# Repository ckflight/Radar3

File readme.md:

# FMCW3 Hardware Design

Custom 6-layer FPGA-based FMCW radar platform designed in KiCad for high-speed radar acquisition, RF processing, and FPGA DSP applications.

The project integrates:

- RF transmitter and dual receiver chains
- ADL5802 mixer stage
- ADA4940 IF signal conditioning
- LTC2292 high-speed ADC
- Artix-7 FPGA processing
- FT2232H USB FIFO streaming
- Multi-rail low-noise power architecture

---

# Overview

FMCW3 is a custom 5.8 GHz FMCW radar hardware platform built around the Xilinx XC7A35T Artix-7 FPGA.

The board is designed for:

- FMCW radar experiments
- SAR imaging
- Doppler processing
- Phase analysis
- FPGA DSP development
- Radar algorithm research

---

# Main Features

## FPGA

- Xilinx XC7A35T-FTG256
- MicroBlaze soft-core support
- SPI Flash boot
- JTAG debugging
- SD card support
- Parallel ADC interface

## RF Front-End

- HMC431LP4 VCO
- Dual RX channels
- ADL5802 active mixer
- Differential IF architecture
- ADA4940 differential amplifiers

## ADC

- LTC2292 dual-channel ADC
- 12-bit parallel interface
- Differential analog inputs
- FPGA synchronous acquisition

## USB

- FT2232H
- FT245 synchronous FIFO mode
- USB Type-C
- High-speed radar data streaming

---

# 6-Layer PCB Design

The board is designed as a controlled impedance 6-layer RF PCB.

## RF Transmission Line Rules

### Single-Ended 50Ω

- JLCPCB:
  - 0.156 mm trace width
- CST Simulation:
  - 0.17 mm trace width

### Differential 50Ω

- 0.4 mm differential pair width/spacing

### USB Differential Pair

- Target impedance:
  - 90Ω differential
- 0.23 mm width
- 0.13 mm spacing

Results:
- ~100Ω on Oshpark
- ~85Ω on JLCPCB

Accepted as operational for USB HS routing.

---

# RF Layout Notes

- Ground pour kept at least:
  - 3× substrate height away from RF traces
- Via stitching placed:
  - ~1 mm beside RF traces
  - ~0.6 mm from trace edge
- LO path uses smooth bends for impedance continuity
- ADC and IF lengths matched for improved phase consistency
- RF clearances and differential routing optimized
- Differential RF routing corrected for proper 50Ω behavior

---

# KiCad Project Structure

```text
FMCW3/
├── fpga.kicad_sch
├── adc.kicad_sch
├── usb.kicad_sch
├── power.kicad_sch
├── mixer.kicad_sch
├── if.kicad_sch
├── tx.kicad_sch
├── rx.kicad_sch
├── fmcw3.kicad_sch
├── fmcw3.kicad_pcb
└── README.md
```

---

# Design Targets

| Parameter | Value |
|---|---|
| Radar Type | FMCW |
| Frequency | 5.8 GHz |
| FPGA | XC7A35T |
| ADC | LTC2292 |
| Mixer | ADL5802 |
| IF Amplifier | ADA4940 |
| USB Interface | FT2232H |
| PCB Stackup | 6 Layer |
| CAD Tool | KiCad 9 |

---

# Related Repositories

FPGA Firmware:
https://github.com/ckflight/FMCW3

Radar Software:
https://github.com/ckflight/FMCW_RADAR

https://github.com/ckflight/FMCW_RADAR_2v2

AI Radar Experiments:
https://github.com/ckflight/RADAR_24GHZ_NEURAL_NETWORK

---

# Author

Cenk KESKİN

---

# License

This project is licensed under the GNU General Public License v3.0 (GPLv3).

You are free to use, modify, and distribute this software under the terms of the GPLv3 license.

Any distributed modifications or derivative works must also be released under the same license and include source code.

For full license text:

https://www.gnu.org/licenses/gpl-3.0.html

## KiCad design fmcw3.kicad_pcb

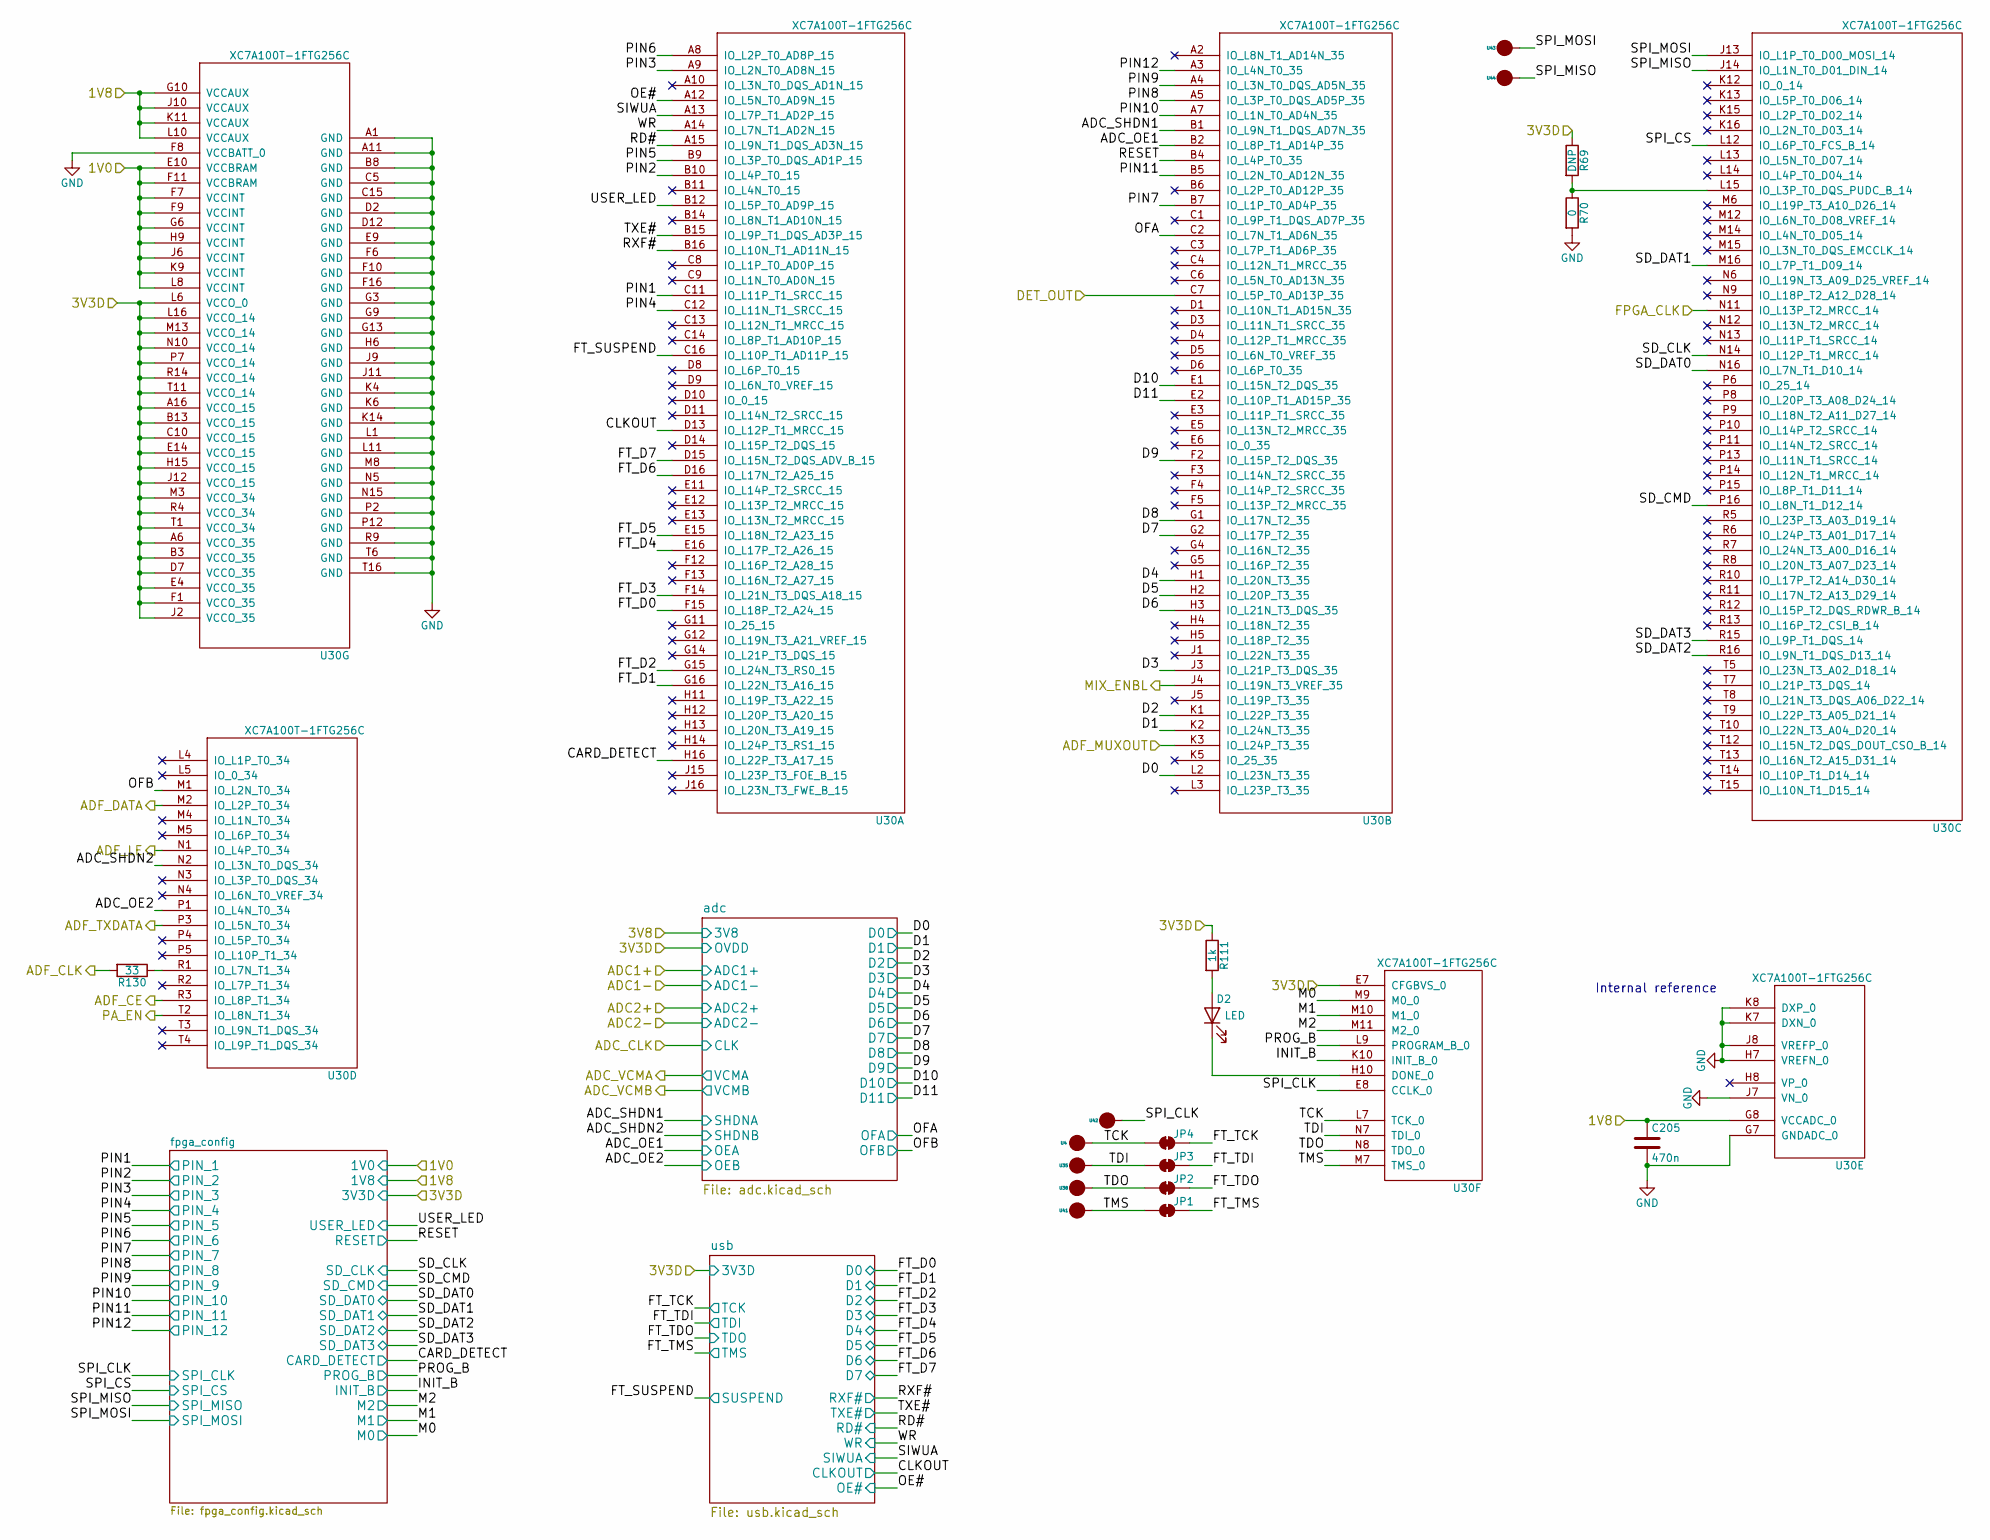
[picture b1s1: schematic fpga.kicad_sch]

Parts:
C205: 470n; SMD_0402
D2: LED; Diode_0603
JP1, JP2, JP3, JP4: SolderJumper_2_Bridged; SolderPad_2_Bridge
R69: DNP; SMD_0402
R70: 0; SMD_0402
R111: 1k; SMD_0402
R130: 33; SMD_0402
U4, U35, U38, U41, U42, U43, U44: SolderPad_1_Circle; SolderPad_1_1.0mm_SMD_Circle
U30: XC7A100T-1FTG256C; FTG256

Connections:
/1V0: U30.E10 (VCCBRAM), U30.F7 (VCCINT), U30.F9 (VCCINT), U30.F11 (VCCBRAM), U30.G6 (VCCINT), U30.H9 (VCCINT), U30.J6 (VCCINT), U30.K9 (VCCINT), U30.L8 (VCCINT); also elsewhere on the board
/1V8: C205.1, U30.G8 (VCCADC_0), U30.G10 (VCCAUX), U30.J10 (VCCAUX), U30.K11 (VCCAUX), U30.L10 (VCCAUX); also elsewhere on the board
/3V3D: R69.1, R111.1, U30.A6 (VCCO_35), U30.A16 (VCCO_15), U30.B3 (VCCO_35), U30.B13 (VCCO_15), U30.C10 (VCCO_15), U30.D7 (VCCO_35), U30.E4 (VCCO_35), U30.E7 (CFGBVS_0), U30.E14 (VCCO_15), U30.F1 (VCCO_35), U30.H15 (VCCO_15), U30.J2 (VCCO_35), U30.J12 (VCCO_15), U30.L6 (VCCO_0), U30.L16 (VCCO_14), U30.M3 (VCCO_34), U30.M13 (VCCO_14), U30.N10 (VCCO_14), U30.P7 (VCCO_14), U30.R4 (VCCO_34), U30.R14 (VCCO_14), U30.T1 (VCCO_34), U30.T11 (VCCO_14); also elsewhere on the board
/ADF_CE: U30.R3 (IO_L8P_T1_34); also elsewhere on the board
/ADF_CLK: R130.2; also elsewhere on the board
/ADF_DATA: U30.M2 (IO_L2P_T0_34); also elsewhere on the board
/ADF_LE: U30.N1 (IO_L4P_T0_34); also elsewhere on the board
/ADF_MUXOUT: U30.K3 (IO_L24P_T3_35); also elsewhere on the board
/ADF_TXDATA: U30.P3 (IO_L5N_T0_34); also elsewhere on the board
/DET_OUT: U30.C7 (IO_L5P_T0_AD13P_35); also elsewhere on the board
/FPGA_CLK: U30.N11 (IO_L13P_T2_MRCC_14); also elsewhere on the board
/MIX_ENBL: U30.J4 (IO_L19N_T3_VREF_35); also elsewhere on the board
/PA_EN: U30.T2 (IO_L8N_T1_34); also elsewhere on the board
/fpga/ADC_OE1: U30.B2 (IO_L8P_T1_AD14P_35); also elsewhere on the board
/fpga/ADC_OE2: U30.P1 (IO_L4N_T0_34); also elsewhere on the board
/fpga/ADC_SHDN1: U30.B1 (IO_L9N_T1_DQS_AD7N_35); also elsewhere on the board
/fpga/ADC_SHDN2: U30.N2 (IO_L3N_T0_DQS_34); also elsewhere on the board
/fpga/CARD_DETECT: U30.H16 (IO_L22P_T3_A17_15); also elsewhere on the board
/fpga/CLKOUT: U30.D13 (IO_L12P_T1_MRCC_15); also elsewhere on the board
/fpga/D0: U30.L2 (IO_L23N_T3_35); also elsewhere on the board
/fpga/D1: U30.K2 (IO_L24N_T3_35); also elsewhere on the board
/fpga/D2: U30.K1 (IO_L22P_T3_35); also elsewhere on the board
/fpga/D3: U30.J3 (IO_L21P_T3_DQS_35); also elsewhere on the board
/fpga/D4: U30.H1 (IO_L20N_T3_35); also elsewhere on the board
/fpga/D5: U30.H2 (IO_L20P_T3_35); also elsewhere on the board
/fpga/D6: U30.H3 (IO_L21N_T3_DQS_35); also elsewhere on the board
/fpga/D7: U30.G2 (IO_L17P_T2_35); also elsewhere on the board
/fpga/D8: U30.G1 (IO_L17N_T2_35); also elsewhere on the board
/fpga/D9: U30.F2 (IO_L15P_T2_DQS_35); also elsewhere on the board
/fpga/D10: U30.E1 (IO_L15N_T2_DQS_35); also elsewhere on the board
/fpga/D11: U30.E2 (IO_L10P_T1_AD15P_35); also elsewhere on the board
/fpga/FT_D0: U30.F15 (IO_L18P_T2_A24_15); also elsewhere on the board
/fpga/FT_D1: U30.G16 (IO_L22N_T3_A16_15); also elsewhere on the board
/fpga/FT_D2: U30.G15 (IO_L24N_T3_RS0_15); also elsewhere on the board
/fpga/FT_D3: U30.F14 (IO_L21N_T3_DQS_A18_15); also elsewhere on the board
/fpga/FT_D4: U30.E16 (IO_L17P_T2_A26_15); also elsewhere on the board
/fpga/FT_D5: U30.E15 (IO_L18N_T2_A23_15); also elsewhere on the board
/fpga/FT_D6: U30.D16 (IO_L17N_T2_A25_15); also elsewhere on the board
/fpga/FT_D7: U30.D15 (IO_L15N_T2_DQS_ADV_B_15); also elsewhere on the board
/fpga/FT_SUSPEND: U30.C16 (IO_L10P_T1_AD11P_15); also elsewhere on the board
/fpga/FT_TCK: JP4.2 (B); also elsewhere on the board
/fpga/FT_TDI: JP3.2 (B); also elsewhere on the board
/fpga/FT_TDO: JP2.2 (B); also elsewhere on the board
/fpga/FT_TMS: JP1.2 (B); also elsewhere on the board
/fpga/INIT_B: U30.K10 (INIT_B_0); also elsewhere on the board
/fpga/M0: U30.M9 (M0_0); also elsewhere on the board
/fpga/M1: U30.M10 (M1_0); also elsewhere on the board
/fpga/M2: U30.M11 (M2_0); also elsewhere on the board
/fpga/OE#: U30.A12 (IO_L5N_T0_AD9N_15); also elsewhere on the board
/fpga/OFA: U30.C2 (IO_L7N_T1_AD6N_35); also elsewhere on the board
/fpga/OFB: U30.M1 (IO_L2N_T0_34); also elsewhere on the board
/fpga/PIN1: U30.C11 (IO_L11P_T1_SRCC_15); also elsewhere on the board
/fpga/PIN2: U30.B10 (IO_L4P_T0_15); also elsewhere on the board
/fpga/PIN3: U30.A9 (IO_L2N_T0_AD8N_15); also elsewhere on the board
/fpga/PIN4: U30.C12 (IO_L11N_T1_SRCC_15); also elsewhere on the board
/fpga/PIN5: U30.B9 (IO_L3P_T0_DQS_AD1P_15); also elsewhere on the board
/fpga/PIN6: U30.A8 (IO_L2P_T0_AD8P_15); also elsewhere on the board
/fpga/PIN7: U30.B7 (IO_L1P_T0_AD4P_35); also elsewhere on the board
/fpga/PIN8: U30.A5 (IO_L3P_T0_DQS_AD5P_35); also elsewhere on the board
/fpga/PIN9: U30.A4 (IO_L3N_T0_DQS_AD5N_35); also elsewhere on the board
/fpga/PIN10: U30.A7 (IO_L1N_T0_AD4N_35); also elsewhere on the board
/fpga/PIN11: U30.B5 (IO_L2N_T0_AD12N_35); also elsewhere on the board
/fpga/PIN12: U30.A3 (IO_L4N_T0_35); also elsewhere on the board
/fpga/PROG_B: U30.L9 (PROGRAM_B_0); also elsewhere on the board
/fpga/RD#: U30.A15 (IO_L9N_T1_DQS_AD3N_15); also elsewhere on the board
/fpga/RESET: U30.B4 (IO_L4P_T0_35); also elsewhere on the board
/fpga/RXF#: U30.B16 (IO_L10N_T1_AD11N_15); also elsewhere on the board
/fpga/SD_CLK: U30.N14 (IO_L12P_T1_MRCC_14); also elsewhere on the board
/fpga/SD_CMD: U30.P16 (IO_L8N_T1_D12_14); also elsewhere on the board
/fpga/SD_DAT0: U30.N16 (IO_L7N_T1_D10_14); also elsewhere on the board
/fpga/SD_DAT1: U30.M16 (IO_L7P_T1_D09_14); also elsewhere on the board
/fpga/SD_DAT2: U30.R16 (IO_L9N_T1_DQS_D13_14); also elsewhere on the board
/fpga/SD_DAT3: U30.R15 (IO_L9P_T1_DQS_14); also elsewhere on the board
/fpga/SIWUA: U30.A13 (IO_L7P_T1_AD2P_15); also elsewhere on the board
/fpga/SPI_CLK: U30.E8 (CCLK_0), U42.1; also elsewhere on the board
/fpga/SPI_CS: U30.L12 (IO_L6P_T0_FCS_B_14); also elsewhere on the board
/fpga/SPI_MISO: U30.J14 (IO_L1N_T0_D01_DIN_14), U44.1; also elsewhere on the board
/fpga/SPI_MOSI: U30.J13 (IO_L1P_T0_D00_MOSI_14), U43.1; also elsewhere on the board
/fpga/TCK: JP4.1 (A), U4.1, U30.L7 (TCK_0)
/fpga/TDI: JP3.1 (A), U30.N7 (TDI_0), U35.1
/fpga/TDO: JP2.1 (A), U30.N8 (TDO_0), U38.1
/fpga/TMS: JP1.1 (A), U30.M7 (TMS_0), U41.1
/fpga/TXE#: U30.B15 (IO_L9P_T1_DQS_AD3P_15); also elsewhere on the board
/fpga/USER_LED: U30.B12 (IO_L5P_T0_AD9P_15); also elsewhere on the board
/fpga/WR: U30.A14 (IO_L7N_T1_AD2N_15); also elsewhere on the board
GND: C205.2, R70.2, U30.A1 (GND), U30.A11 (GND), U30.B8 (GND), U30.C5 (GND), U30.C15 (GND), U30.D2 (GND), U30.D12 (GND), U30.E9 (GND), U30.F6 (GND), U30.F8 (VCCBATT_0), U30.F10 (GND), U30.F16 (GND), U30.G3 (GND), U30.G7 (GNDADC_0), U30.G9 (GND), U30.G13 (GND), U30.H6 (GND), U30.H7 (VREFN_0), U30.J7 (VN_0), U30.J8 (VREFP_0), U30.J9 (GND), U30.J11 (GND), U30.K4 (GND), U30.K6 (GND), U30.K7 (DXN_0), U30.K8 (DXP_0), U30.K14 (GND), U30.L1 (GND), U30.L11 (GND), U30.M8 (GND), U30.N5 (GND), U30.N15 (GND), U30.P2 (GND), U30.P12 (GND), U30.R9 (GND), U30.T6 (GND), U30.T16 (GND); also elsewhere on the board
unnamed: D2.2 (A), R111.2
unnamed: D2.1 (K), U30.H10 (DONE_0)
unnamed: R69.2, R70.1, U30.L15 (IO_L3P_T0_DQS_PUDC_B_14)
unnamed: R130.1, U30.R1 (IO_L7N_T1_34)

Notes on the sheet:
Internal reference

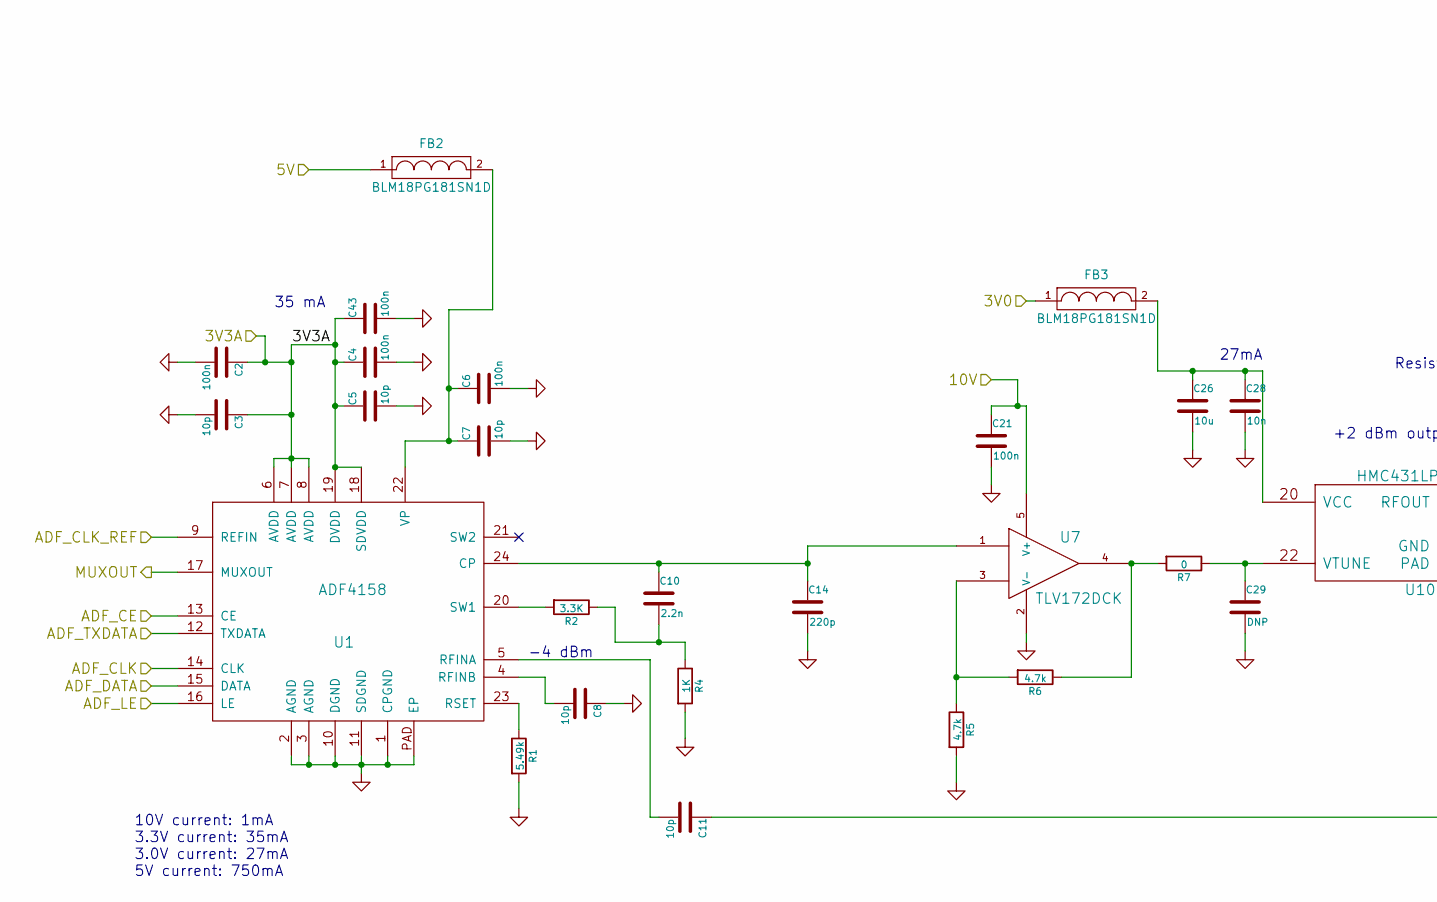
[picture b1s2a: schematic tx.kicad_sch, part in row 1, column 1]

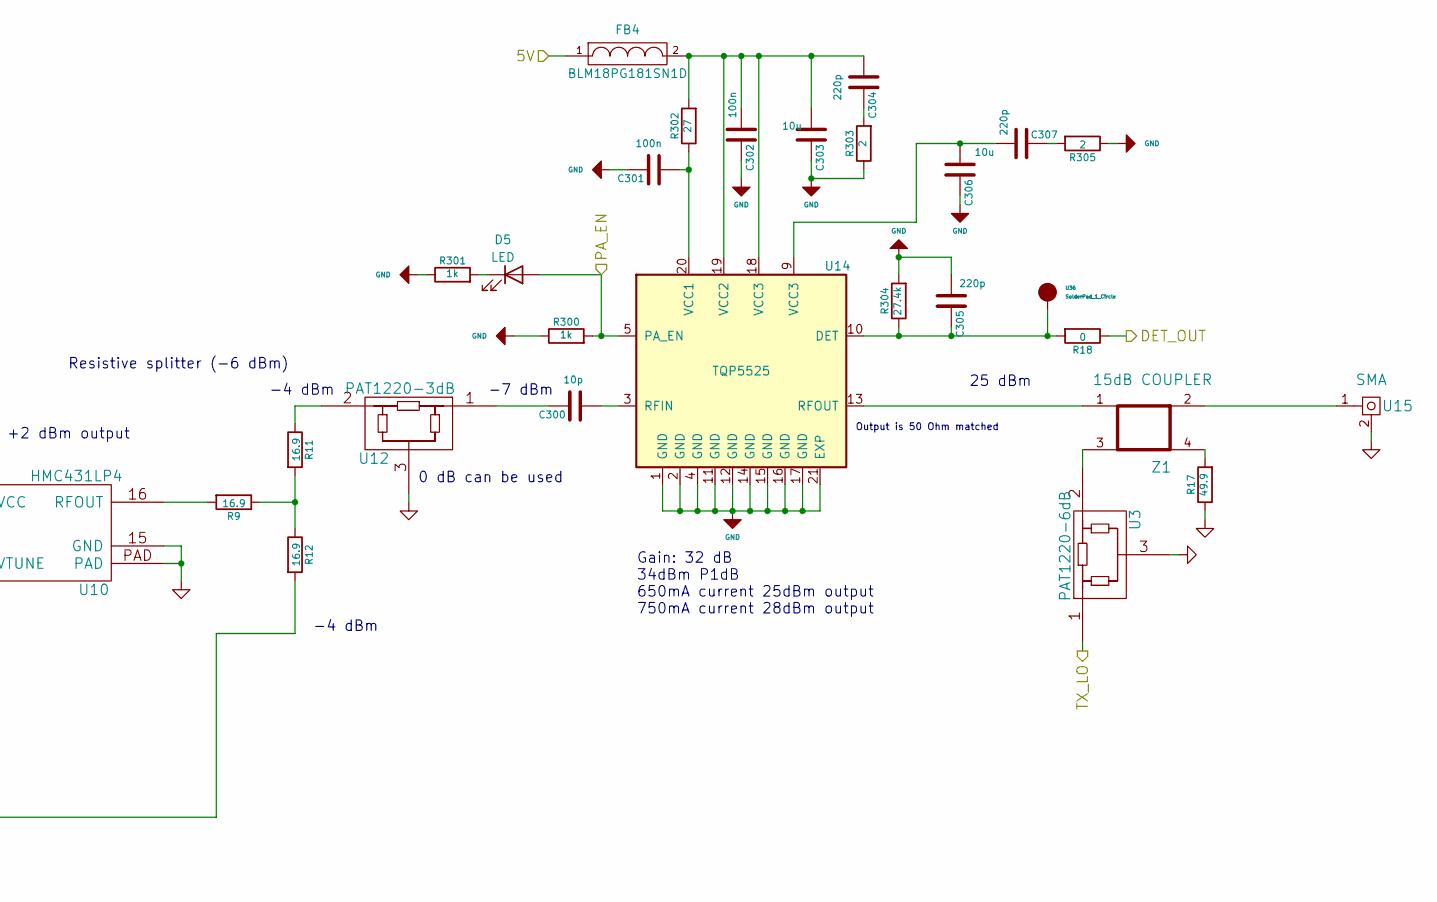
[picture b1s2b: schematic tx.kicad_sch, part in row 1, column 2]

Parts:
C2, C4, C6, C21, C43, C301, C302: 100n; SMD_0402
C3, C5, C7, C8, C11, C300: 10p; SMD_0402
C10: 2.2n; SMD_0402
C14, C304, C305, C307: 220p; SMD_0402
C26, C303, C306: 10u; SMD_0805
C28: 10n; SMD_0402
C29: DNP; SMD_0402
D5: LED; Diode_0603
FB2, FB3, FB4: BLM18PG181SN1D; SMD_0603
R1: 5.49k; SMD_0402
R2: 3.3K; SMD_0402
R4: 1K; SMD_0402
R5, R6: 4.7k; SMD_0402
R7, R18: 0; SMD_0402
R9, R11, R12: 16.9; SMD_0402
R17: 49.9; SMD_0402
R300, R301: 1k; SMD_0402
R302: 27; SMD_0402
R303, R305: 2; SMD_0603
R304: 27.4k; SMD_0402
U1: ADF4158; VFQFN-24
U3: PAT1220-6dB; PAT1220
U7: TLV172DCK; SOT-353_SC-70-5
U10: HMC431LP4; VQFN-24
U12: PAT1220-3dB; PAT1220
U14: TQP5525; QFN-20-1EP_4x4mm_P0.5mm_EP2.5x2.5mm_ThermalVias
U15: SMA; CONSMA003.062
U36: SolderPad_1_Circle; SolderPad_1_1.5mm_SMD_Circle
Z1: 15dB COUPLER; Directional_Coupler_15dB_0.169mm_v2

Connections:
/3V0: FB3.1; also elsewhere on the board
/3V3A: C2.1, C3.1, C4.1, C5.1, C43.1, U1.6 (AVDD), U1.7 (AVDD), U1.8 (AVDD), U1.18 (SDVDD), U1.19 (DVDD); also elsewhere on the board
/5V: FB2.1, FB4.1; also elsewhere on the board
/10V: C21.1, U7.5 (V+); also elsewhere on the board
/ADF_CE: U1.13 (CE); also elsewhere on the board
/ADF_CLK: U1.14 (CLK); also elsewhere on the board
/ADF_CLK_REF: U1.9 (REFIN); also elsewhere on the board
/ADF_DATA: U1.15 (DATA); also elsewhere on the board
/ADF_LE: U1.16 (LE); also elsewhere on the board
/ADF_MUXOUT: U1.17 (MUXOUT); also elsewhere on the board
/ADF_TXDATA: U1.12 (TXDATA); also elsewhere on the board
/DET_OUT: R18.1; also elsewhere on the board
/LO: U3.1; also elsewhere on the board
/PA_EN: D5.2 (A), R300.2, U14.5 (PA_EN); also elsewhere on the board
GND: C2.2, C3.2, C4.2, C5.2, C6.2, C7.2, C8.1, C14.2, C21.2, C26.2, C28.2, C29.2, C43.2, C301.1, C302.1, C303.1, C305.2, C306.1, R1.2, R4.2, R5.2, R17.1, R300.1, R301.1, R303.1, R304.2, R305.1, U1.1 (CPGND), U1.2 (AGND), U1.3 (AGND), U1.10 (DGND), U1.11 (SDGND), U1.PAD (EP), U3.3, U7.2 (V-), U10.15 (GND), U10.PAD, U12.3, U14.1 (GND), U14.2 (GND), U14.4 (GND), U14.11 (GND), U14.12 (GND), U14.14 (GND), U14.15 (GND), U14.16 (GND), U14.17 (GND), U14.21 (EXP), U15.2; also elsewhere on the board
unnamed: C10.2, R2.1, R4.1
unnamed: C11.1, R12.2
unnamed: C300.1, U12.1
unnamed: C304.1, R303.2
unnamed: C306.2, C307.2, U14.9 (VCC3)
unnamed: C307.1, R305.2
unnamed: D5.1 (K), R301.2
unnamed: R5.1, R6.2, U7.3
unnamed: R6.1, R7.2, U7.4
unnamed: R11.1, U12.2
unnamed: R9.1, R11.2, R12.1
unnamed: R17.2, Z1.4
unnamed: C10.1, C14.1, U1.24 (CP), U7.1
unnamed: C11.2, U1.5 (RFINA)
unnamed: C8.2, U1.4 (RFINB)
unnamed: R1.1, U1.23 (RSET)
unnamed: R2.2, U1.20 (SW1)
unnamed: C6.1, C7.1, FB2.2, U1.22 (VP)
unnamed: U3.2, Z1.3
unnamed: R9.2, U10.16 (RFOUT)
unnamed: C26.1, C28.1, FB3.2, U10.20 (VCC)
unnamed: C29.1, R7.1, U10.22 (VTUNE)
unnamed: C305.1, R18.2, R304.1, U14.10 (DET), U36.1
unnamed: C300.2, U14.3 (RFIN)
unnamed: U14.13 (RFOUT), Z1.1
unnamed: C301.2, R302.1, U14.20 (VCC1)
unnamed: C302.2, C303.2, C304.2, FB4.2, R302.2, U14.18 (VCC3), U14.19 (VCC2)
unnamed: U15.1, Z1.2

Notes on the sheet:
Resistive splitter (-6 dBm)
-4 dBm
10V current: 1mA 3.3V current: 35mA 3.0V current: 27mA 5V current: 750mA
+2 dBm output
35 mA
-7 dBm
27mA
Output is 50 Ohm matched
Gain: 32 dB 34dBm P1dB 650mA current 25dBm output 750mA current 28dBm output
0 dB can be used
25 dBm

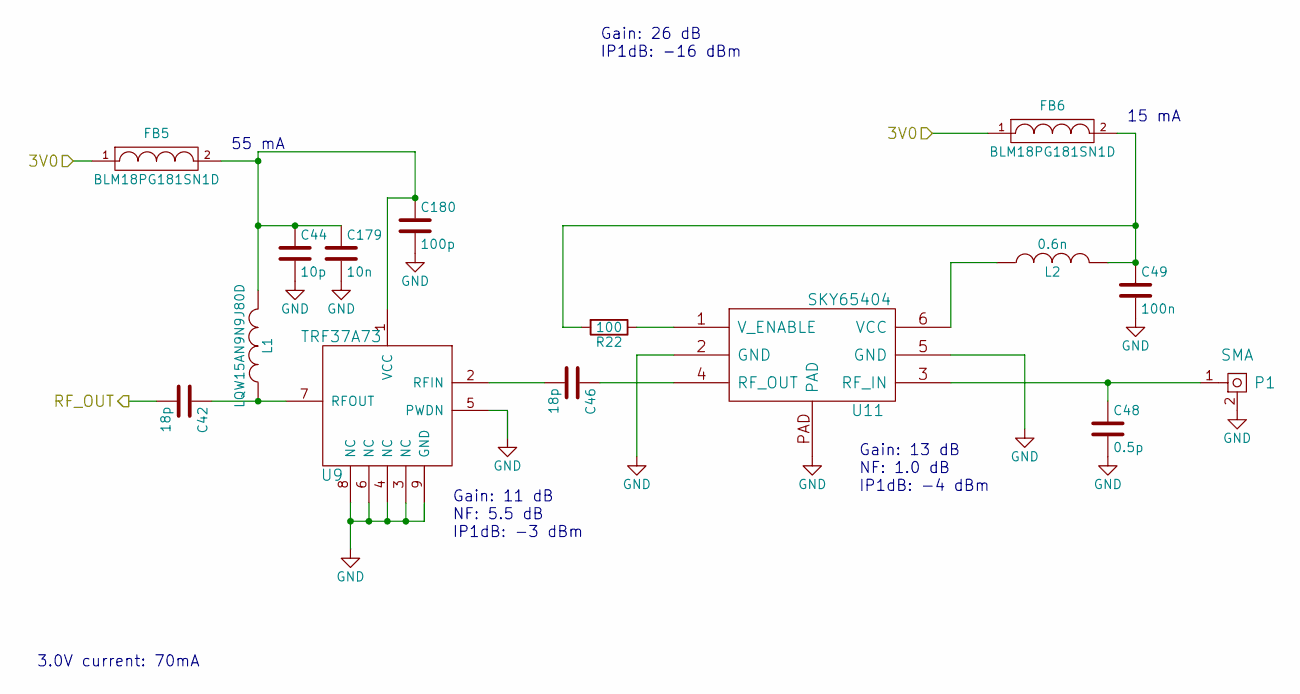
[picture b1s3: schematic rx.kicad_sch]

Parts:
C42, C46: 18p; SMD_0402
C44: 10p; SMD_0402
C48: 0.5p; SMD_0402
C49: 100n; SMD_0402
C179: 10n; SMD_0402
C180: 100p; SMD_0402
FB5, FB6: BLM18PG181SN1D; SMD_0603
L1: LQW15AN9N9J80D; SMD_0402
L2: 0.6n; SMD_0402
P1: SMA; CONSMA003.062
R22: 100; SMD_0402
U9: TRF37A73; DFN-8-1EP_2x2mm_Pitch0.5mm
U11: SKY65404; XFDFN-6

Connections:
/3V0: FB5.1, FB6.1; also elsewhere on the board
/RF1: C42.2; also elsewhere on the board
GND: C44.2, C48.2, C49.2, C179.2, C180.2, P1.2, U9.3 (NC), U9.4 (NC), U9.5 (PWDN), U9.6 (NC), U9.8 (NC), U9.9 (GND), U11.2 (GND), U11.5 (GND), U11.PAD; also elsewhere on the board
unnamed: C49.1, FB6.2, L2.2, R22.2
unnamed: C46.2, U9.2 (RFIN)
unnamed: C42.1, L1.1, U9.7 (RFOUT)
unnamed: C44.1, C179.1, C180.1, FB5.2, L1.2, U9.1 (VCC)
unnamed: C48.1, P1.1, U11.3 (RF_IN)
unnamed: C46.1, U11.4 (RF_OUT)
unnamed: L2.1, U11.6 (VCC)
unnamed: R22.1, U11.1 (V_ENABLE)

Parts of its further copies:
C52, C55: 18p; SMD_0402
C53: 10p; SMD_0402
C57: 0.5p; SMD_0402
C58: 100n; SMD_0402
C206: 10n; SMD_0402
C213: 100p; SMD_0402
FB7, FB8: BLM18PG181SN1D; SMD_0603
L3: LQW15AN9N9J80D; SMD_0402
L4: 0.6n; SMD_0402
P2: SMA; CONSMA003.062
R23: 100; SMD_0402
U13: TRF37A73; DFN-8-1EP_2x2mm_Pitch0.5mm
U16: SKY65404; XFDFN-6

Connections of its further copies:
/3V0: FB7.1, FB8.1; also elsewhere on the board
/RF2: C52.2; also elsewhere on the board
GND: C53.2, C57.2, C58.2, C206.2, C213.2, P2.2, U13.3 (NC), U13.4 (NC), U13.5 (PWDN), U13.6 (NC), U13.8 (NC), U13.9 (GND), U16.2 (GND), U16.5 (GND), U16.PAD; also elsewhere on the board
unnamed: C58.1, FB8.2, L4.2, R23.2
unnamed: C55.2, U13.2 (RFIN)
unnamed: C52.1, L3.1, U13.7 (RFOUT)
unnamed: C53.1, C206.1, C213.1, FB7.2, L3.2, U13.1 (VCC)
unnamed: C57.1, P2.1, U16.3 (RF_IN)
unnamed: C55.1, U16.4 (RF_OUT)
unnamed: L4.1, U16.6 (VCC)
unnamed: R23.1, U16.1 (V_ENABLE)

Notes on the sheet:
Gain: 11 dB NF: 5.5 dB IP1dB: -3 dBm
15 mA
Gain: 13 dB NF: 1.0 dB IP1dB: -4 dBm
3.0V current: 70mA
55 mA
Gain: 26 dB IP1dB: -16 dBm

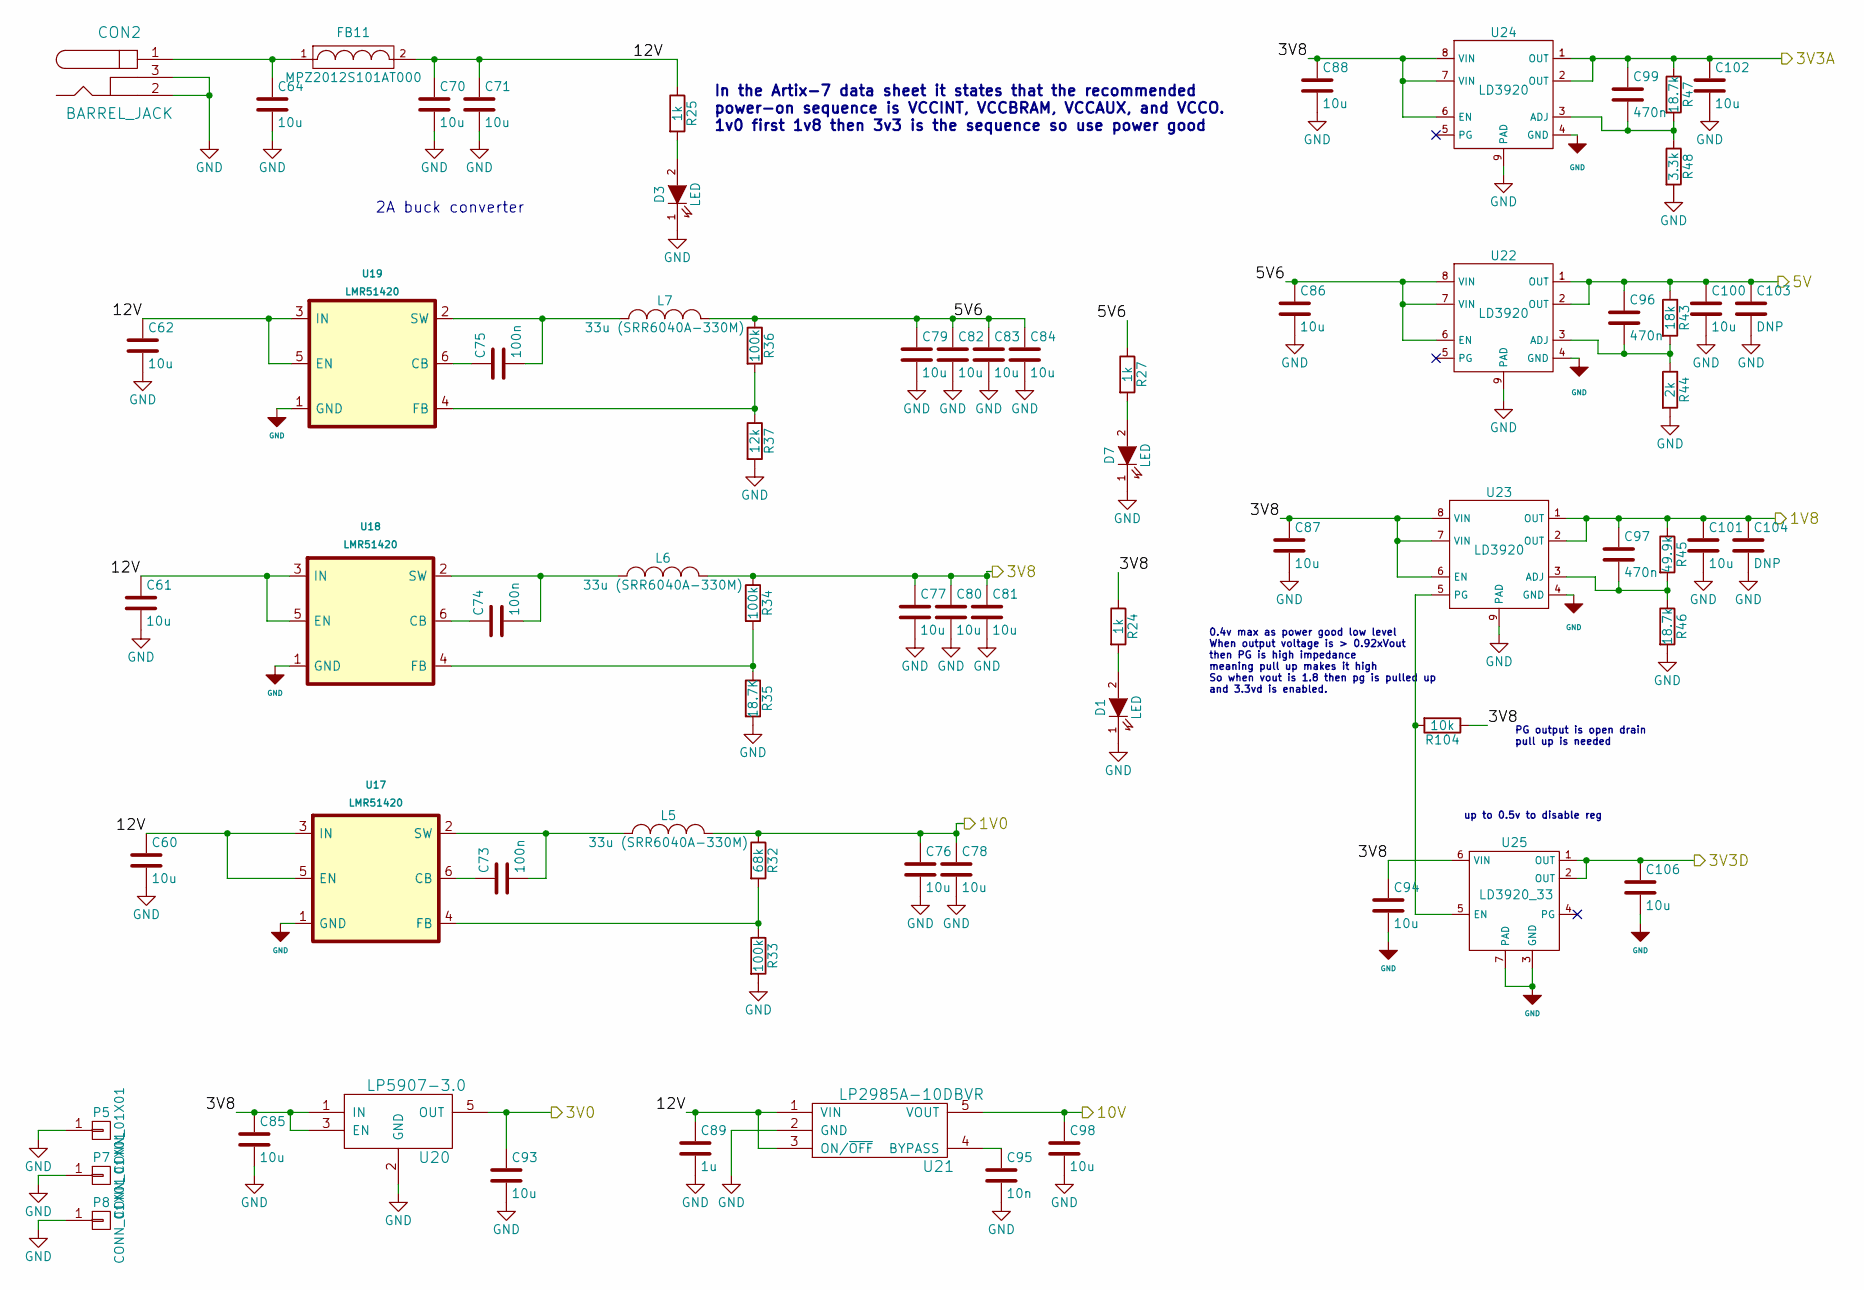
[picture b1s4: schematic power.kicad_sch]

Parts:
C60, C61, C62, C64, C70, C71, C76, C77, C78, C79, C80, C81, C82, C83, C84, C85, C86, C87, C88, C93, C94, C98, C100, C101, C102, C106: 10u; SMD_0805
C73, C74, C75: 100n; SMD_0402
C89: 1u; SMD_0603
C95: 10n; SMD_0402
C96, C97, C99: 470n; SMD_0402
C103, C104: DNP; SMD_0805
CON2: BARREL_JACK; BarrelJack
D1, D3, D7: LED; Diode_0603
FB11: MPZ2012S101AT000; SMD_0805
L5, L6, L7: 33u (SRR6040A-330M); SRR6040A
P5, P7, P8: CONN_01X01; MountingHole_3.2mm_M3_Pad_Via_mod
R24, R25, R27: 1k; SMD_0402
R32: 68k; SMD_0402
R33, R34, R36: 100k; SMD_0402
R35: 18.7K; SMD_0402
R37: 12k; SMD_0402
R43: 18k; SMD_0402
R44: 2k; SMD_0402
R45: 49.9k; SMD_0402
R46, R47: 18.7k; SMD_0402
R48: 3.3k; SMD_0402
R104: 10k; SMD_0402
U17, U18, U19: LMR51420; SOT23_6
U20: LP5907-3.0; SOT-23-5
U21: LP2985A-10DBVR; SOT-23-5
U22, U23, U24: LD3920; DFN-8-1EP_4x4mm_P0.8mm_EP2.3x3.24mm
U25: LD3920_33; DFN-6-1EP_3x3mm_P0.95mm_EP1.7x2.6mm

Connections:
/1V0: C76.1, C78.1, L5.2, R32.1; also elsewhere on the board
/1V8: C97.1, C101.1, C104.1, R45.1, U23.1 (OUT), U23.2 (OUT); also elsewhere on the board
/3V0: C93.1, U20.5 (OUT); also elsewhere on the board
/3V3A: C99.1, C102.1, R47.1, U24.1 (OUT), U24.2 (OUT); also elsewhere on the board
/3V3D: C106.1, U25.1 (OUT), U25.2 (OUT); also elsewhere on the board
/3V8: C77.1, C80.1, C81.1, C85.1, C87.1, C88.1, C94.1, L6.2, R24.1, R34.1, R104.1, U20.1 (IN), U20.3 (EN), U23.6 (EN), U23.7 (VIN), U23.8 (VIN), U24.6 (EN), U24.7 (VIN), U24.8 (VIN), U25.6 (VIN); also elsewhere on the board
/5V: C96.1, C100.1, C103.1, R43.1, U22.1 (OUT), U22.2 (OUT); also elsewhere on the board
/10V: C98.1, U21.5 (VOUT); also elsewhere on the board
/power/5V6: C79.1, C82.1, C83.1, C84.1, C86.1, L7.2, R27.1, R36.1, U22.6 (EN), U22.7 (VIN), U22.8 (VIN)
/power/12V: C60.1, C61.1, C62.1, C70.1, C71.1, C89.1, FB11.2, R25.1, U17.3 (IN), U17.5 (EN), U18.3 (IN), U18.5 (EN), U19.3 (IN), U19.5 (EN), U21.1 (VIN), U21.3 (ON/~OFF)
GND: C60.2, C61.2, C62.2, C64.2, C70.2, C71.2, C76.2, C77.2, C78.2, C79.2, C80.2, C81.2, C82.2, C83.2, C84.2, C85.2, C86.2, C87.2, C88.2, C89.2, C93.2, C94.2, C95.2, C98.2, C100.2, C101.2, C102.2, C103.2, C104.2, C106.2, CON2.2, CON2.3, D1.1 (K), D3.1 (K), D7.1 (K), P5.1, P7.1, P8.1, R33.2, R35.2, R37.2, R44.2, R46.2, R48.2, U17.1 (GND), U18.1 (GND), U19.1 (GND), U20.2 (GND), U21.2 (GND), U22.4 (GND), U22.9 (PAD), U23.4 (GND), U23.9 (PAD), U24.4 (GND), U24.9 (PAD), U25.3 (GND), U25.7 (PAD); also elsewhere on the board
unnamed: C64.1, CON2.1, FB11.1
unnamed: D1.2 (A), R24.2
unnamed: D3.2 (A), R25.2
unnamed: D7.2 (A), R27.2
unnamed: C73.1, U17.6 (CB)
unnamed: R32.2, R33.1, U17.4 (FB)
unnamed: C73.2, L5.1, U17.2 (SW)
unnamed: C74.1, U18.6 (CB)
unnamed: R34.2, R35.1, U18.4 (FB)
unnamed: C74.2, L6.1, U18.2 (SW)
unnamed: C75.1, U19.6 (CB)
unnamed: R36.2, R37.1, U19.4 (FB)
unnamed: C75.2, L7.1, U19.2 (SW)
unnamed: C95.1, U21.4 (BYPASS)
unnamed: C96.2, R43.2, R44.1, U22.3 (ADJ)
unnamed: C97.2, R45.2, R46.1, U23.3 (ADJ)
unnamed: R104.2, U23.5 (PG), U25.5 (EN)
unnamed: C99.2, R47.2, R48.1, U24.3 (ADJ)

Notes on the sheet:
up to 0.5v to disable reg
0.4v max as power good low level When output voltage is > 0.92xVout then PG is high impedance meaning pull up makes it high So when vout is 1.8 then pg is pulled up and 3.3vd is enabled.
PG output is open drain pull up is needed
In the Artix-7 data sheet it states that the recommended power-on sequence is VCCINT, VCCBRAM, VCCAUX, and VCCO. 1v0 first 1v8 then 3v3 is the sequence so use power good
2A buck converter

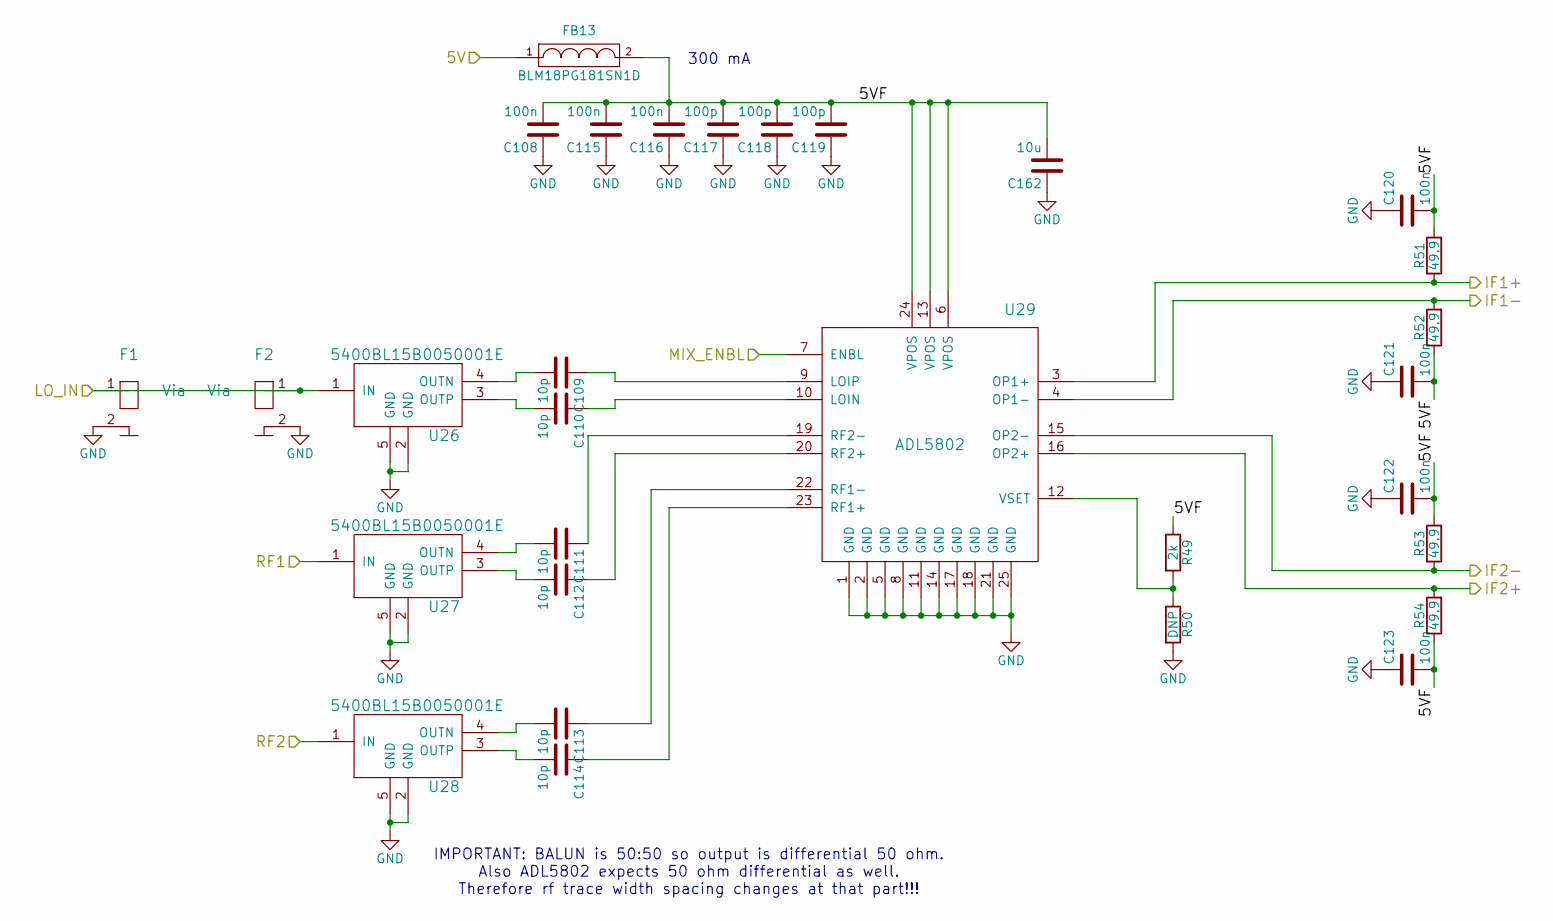
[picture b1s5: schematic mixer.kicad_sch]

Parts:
C108, C115, C116, C120, C121, C122, C123: 100n; SMD_0402
C109, C110, C111, C112, C113, C114: 10p; SMD_0402
C117, C118, C119: 100p; SMD_0402
C162: 10u; SMD_0805
F1, F2: Via; RF_via
FB13: BLM18PG181SN1D; SMD_0603
R49: 2k; SMD_0402
R50: DNP; SMD_0402
R51, R52, R53, R54: 49.9; SMD_0402
U26, U27, U28: 5400BL15B0050001E; 5400BL15B050E
U29: ADL5802; QFN-24-1EP_4x4mm_Pitch0.5mm

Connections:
/5V: FB13.1; also elsewhere on the board
/LO: F1.1, F2.1, U26.1 (IN); also elsewhere on the board
/MIX_ENBL: U29.7 (ENBL); also elsewhere on the board
/RF1: U27.1 (IN); also elsewhere on the board
/RF2: U28.1 (IN); also elsewhere on the board
/mixer/5VF: C108.2, C115.2, C116.2, C117.2, C118.2, C119.2, C120.2, C121.2, C122.2, C123.2, C162.2, FB13.2, R49.1, R51.2, R52.1, R53.2, R54.1, U29.6 (VPOS), U29.13 (VPOS), U29.24 (VPOS)
/mixer/IF1+: R51.1, U29.3 (OP1+); also elsewhere on the board
/mixer/IF1-: R52.2, U29.4 (OP1-); also elsewhere on the board
/mixer/IF2+: R54.2, U29.16 (OP2+); also elsewhere on the board
/mixer/IF2-: R53.1, U29.15 (OP2-); also elsewhere on the board
GND: C108.1, C115.1, C116.1, C117.1, C118.1, C119.1, C120.1, C121.1, C122.1, C123.1, C162.1, F1.2, F2.2, R50.2, U26.2 (GND), U26.5 (GND), U27.2 (GND), U27.5 (GND), U28.2 (GND), U28.5 (GND), U29.1 (GND), U29.2 (GND), U29.5 (GND), U29.8 (GND), U29.11 (GND), U29.14 (GND), U29.17 (GND), U29.18 (GND), U29.21 (GND), U29.25 (GND); also elsewhere on the board
unnamed: C109.2, U26.4 (OUTN)
unnamed: C110.2, U26.3 (OUTP)
unnamed: C111.2, U27.4 (OUTN)
unnamed: C112.2, U27.3 (OUTP)
unnamed: C113.2, U28.4 (OUTN)
unnamed: C114.2, U28.3 (OUTP)
unnamed: C110.1, U29.10 (LOIN)
unnamed: C109.1, U29.9 (LOIP)
unnamed: C114.1, U29.23 (RF1+)
unnamed: C113.1, U29.22 (RF1-)
unnamed: C112.1, U29.20 (RF2+)
unnamed: C111.1, U29.19 (RF2-)
unnamed: R49.2, R50.1, U29.12 (VSET)

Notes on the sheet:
300 mA
IMPORTANT: BALUN is 50:50 so output is differential 50 ohm. Also ADL5802 expects 50 ohm differential as well. Therefore rf trace width spacing changes at that part!!!
